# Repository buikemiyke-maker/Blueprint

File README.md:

a" />

# Custom Macropad with Rotary Encoder
BOM:
Seed Studio XIAO RP2040 1X,
Mechanical key switches 6X,
Rotary encoder with push switch 1X,
SK6812 Mini RGB LED 2X,
PCB (custom) 1X,
Soldering iron 1X,
Solder wire 1X,
Flux 1x,
Tweezers 1x,
3d Printed case (all layers) 1x,
Rubber Feet 4x,
Screws 4x,
Rotary encoder knob 1x,
Key caps 4x.

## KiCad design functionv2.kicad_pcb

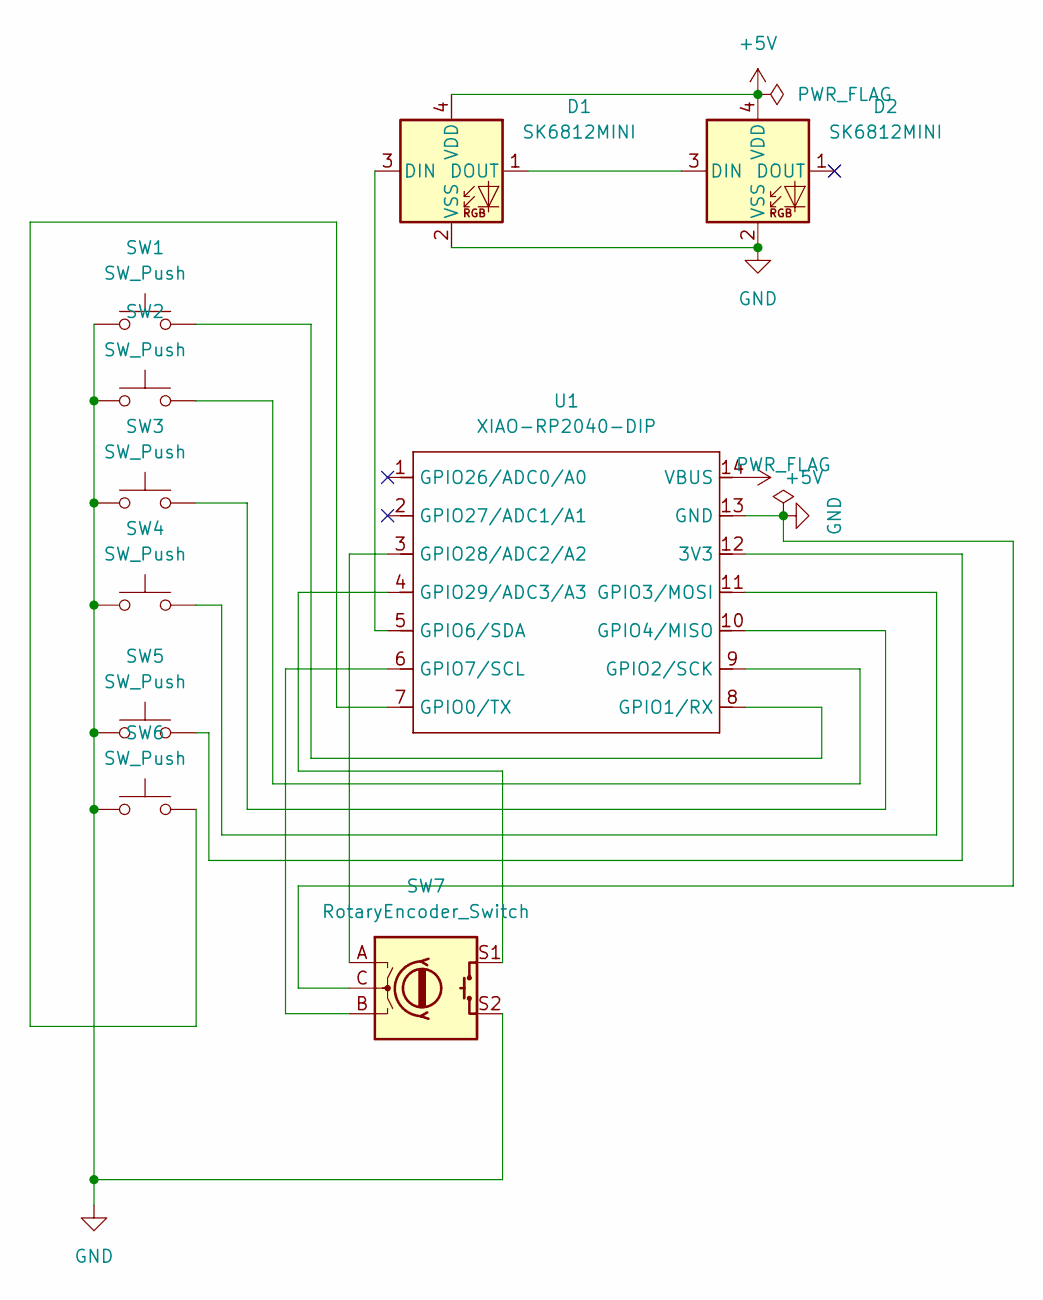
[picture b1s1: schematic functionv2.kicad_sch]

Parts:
D1, D2: SK6812MINI; LED_SK6812MINI_PLCC4_3.5x3.5mm_P1.75mm
SW1, SW2, SW3, SW4, SW5, SW6: SW_Push; SW_Cherry_MX_1.00u_PCB
SW7: RotaryEncoder_Switch; RotaryEncoder_Alps_EC11E-Switch_Vertical_H20mm
U1: XIAO-RP2040-DIP

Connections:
+5V: D1.4 (VDD), D2.4 (VDD), U1.14 (VBUS)
GND: D1.2 (VSS), D2.2 (VSS), SW1.1, SW2.1, SW3.1, SW4.1, SW5.1, SW6.1, SW7.C, SW7.S2, U1.13 (GND)
unnamed: D1.3 (DIN), U1.5 (GPIO6/SDA)
unnamed: D1.1 (DOUT), D2.3 (DIN)
unnamed: SW5.2, U1.12 (3V3)
unnamed: SW6.2, U1.7 (GPIO0/TX)
unnamed: SW1.2, U1.8 (GPIO1/RX)
unnamed: SW2.2, U1.9 (GPIO2/SCK)
unnamed: SW4.2, U1.11 (GPIO3/MOSI)
unnamed: SW3.2, U1.10 (GPIO4/MISO)
unnamed: SW7.B, U1.6 (GPIO7/SCL)
unnamed: SW7.A, U1.3 (GPIO28/ADC2/A2)
unnamed: SW7.S1, U1.4 (GPIO29/ADC3/A3)

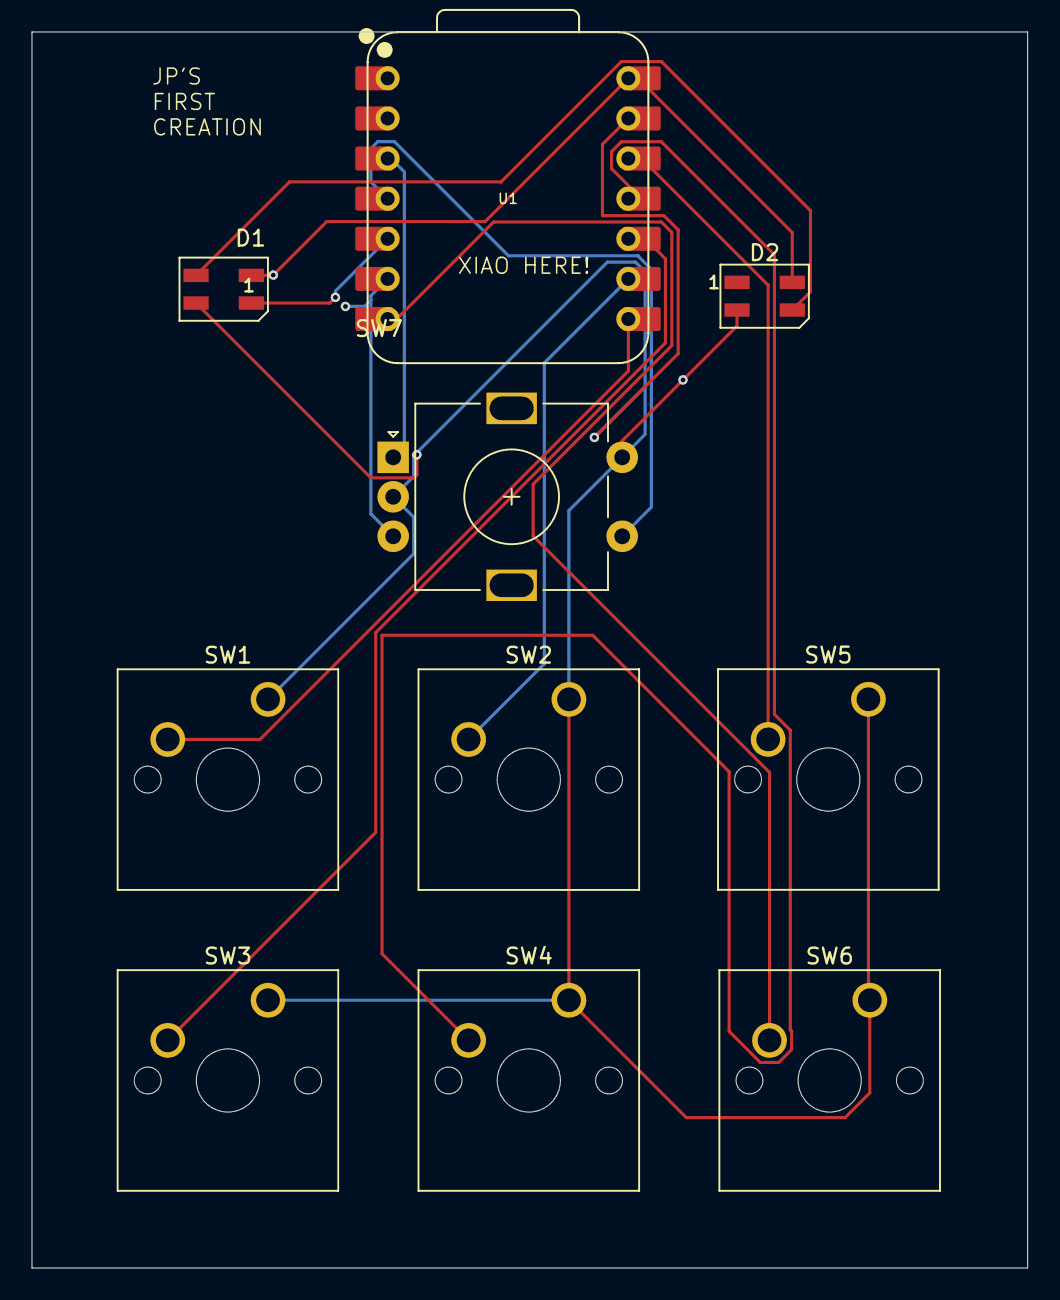
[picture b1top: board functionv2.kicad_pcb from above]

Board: 2 copper layers, 63.0 x 78.3 mm, 10 parts (0 on the bottom side), 13 nets.

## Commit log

2025-12-23 Rename function.step to schematics/function.step
2025-12-23 Rename functionv2.kicad_pro to schematics/functionv2.kicad_pro
2025-12-23 Rename CASING.f3d to models/CASING.f3d
2025-12-23 Rename outer.f3d to models/outer.f3d
2025-12-23 Rename Main.py to firmware/Main.py
2025-12-23 Create with components
